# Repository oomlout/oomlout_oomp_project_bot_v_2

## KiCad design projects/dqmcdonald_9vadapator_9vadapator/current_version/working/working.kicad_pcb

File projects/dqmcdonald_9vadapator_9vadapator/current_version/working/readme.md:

# 9vadapator
 
## summary 
* id: dqmcdonald_9vadapator_9vadapator
* user: dqmcdonald
* name: 9vadapator
* board: 9vadapator
* repo: https://github.com/dqmcdonald/9VAdapator
* src_file_repo_kicad_pcb: 9VAdapator.kicad_pcb
* src_file_repo_kicad_pcb_link: https://github.com/dqmcdonald/9VAdapator/tree/master/9VAdapator.kicad_pcb

* src_file_repo_sch: 9VAdapator.sch
* src_file_repo_sch_link: https://github.com/dqmcdonald/9VAdapator/tree/master/9VAdapator.sch
* full details link: https://github.com/oomlout/oomlout_oomp_project_bot_v_2/tree/main/projects/dqmcdonald_9vadapator_9vadapator/current_version/working

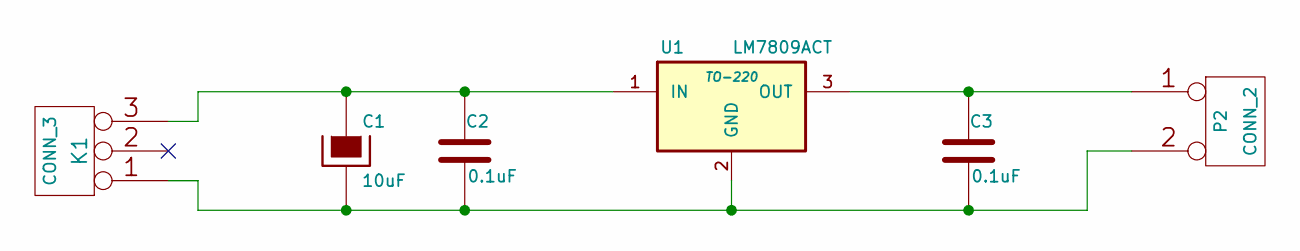
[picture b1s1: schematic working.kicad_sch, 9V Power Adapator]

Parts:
C1: 10uF
C2, C3: 0.1uF
K1: CONN_3
P2: CONN_2
U1: LM7809ACT; TO-220

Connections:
unnamed: C1.1, C2.1, K1.3, U1.1 (IN)
unnamed: C1.2, C2.2, C3.2, K1.1, P2.2 (GND), U1.2 (GND)
unnamed: C3.1, P2.1 (VCC), U1.3 (OUT)

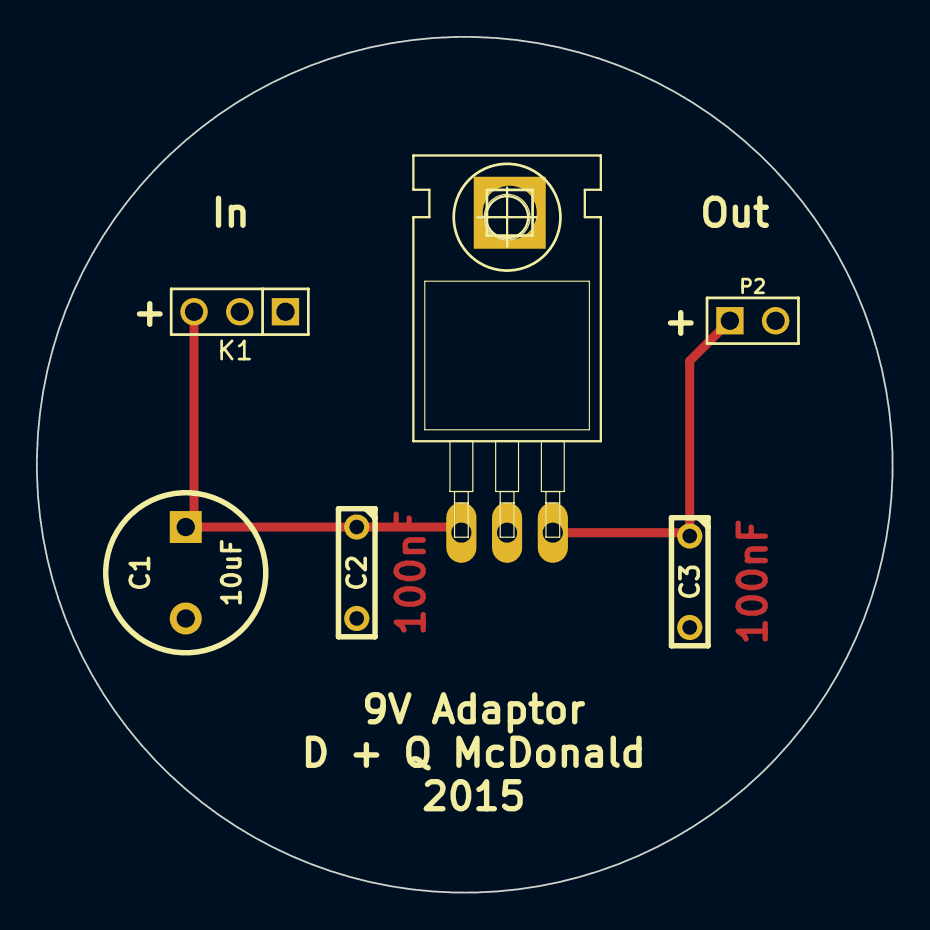
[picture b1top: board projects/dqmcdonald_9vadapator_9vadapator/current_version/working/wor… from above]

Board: 2 copper layers, 47.5 x 47.5 mm, 6 parts (0 on the bottom side), 3 nets.

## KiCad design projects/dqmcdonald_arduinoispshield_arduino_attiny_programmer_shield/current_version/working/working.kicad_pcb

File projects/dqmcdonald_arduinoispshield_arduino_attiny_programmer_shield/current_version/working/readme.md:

# arduinoispshield
 
## summary 
* id: dqmcdonald_arduinoispshield_arduino_attiny_programmer_shield
* user: dqmcdonald
* name: arduinoispshield
* board: arduino_attiny_programmer_shield
* repo: https://github.com/dqmcdonald/ArduinoISPShield
* src_file_repo_kicad_pcb: Arduino ATTINY Programmer Shield.kicad_pcb
* src_file_repo_kicad_pcb_link: https://github.com/dqmcdonald/ArduinoISPShield/tree/master/Arduino ATTINY Programmer Shield.kicad_pcb

* src_file_repo_sch: Arduino ATTINY Programmer Shield.sch
* src_file_repo_sch_link: https://github.com/dqmcdonald/ArduinoISPShield/tree/master/Arduino ATTINY Programmer Shield.sch
* full details link: https://github.com/oomlout/oomlout_oomp_project_bot_v_2/tree/main/projects/dqmcdonald_arduinoispshield_arduino_attiny_programmer_shield/current_version/working

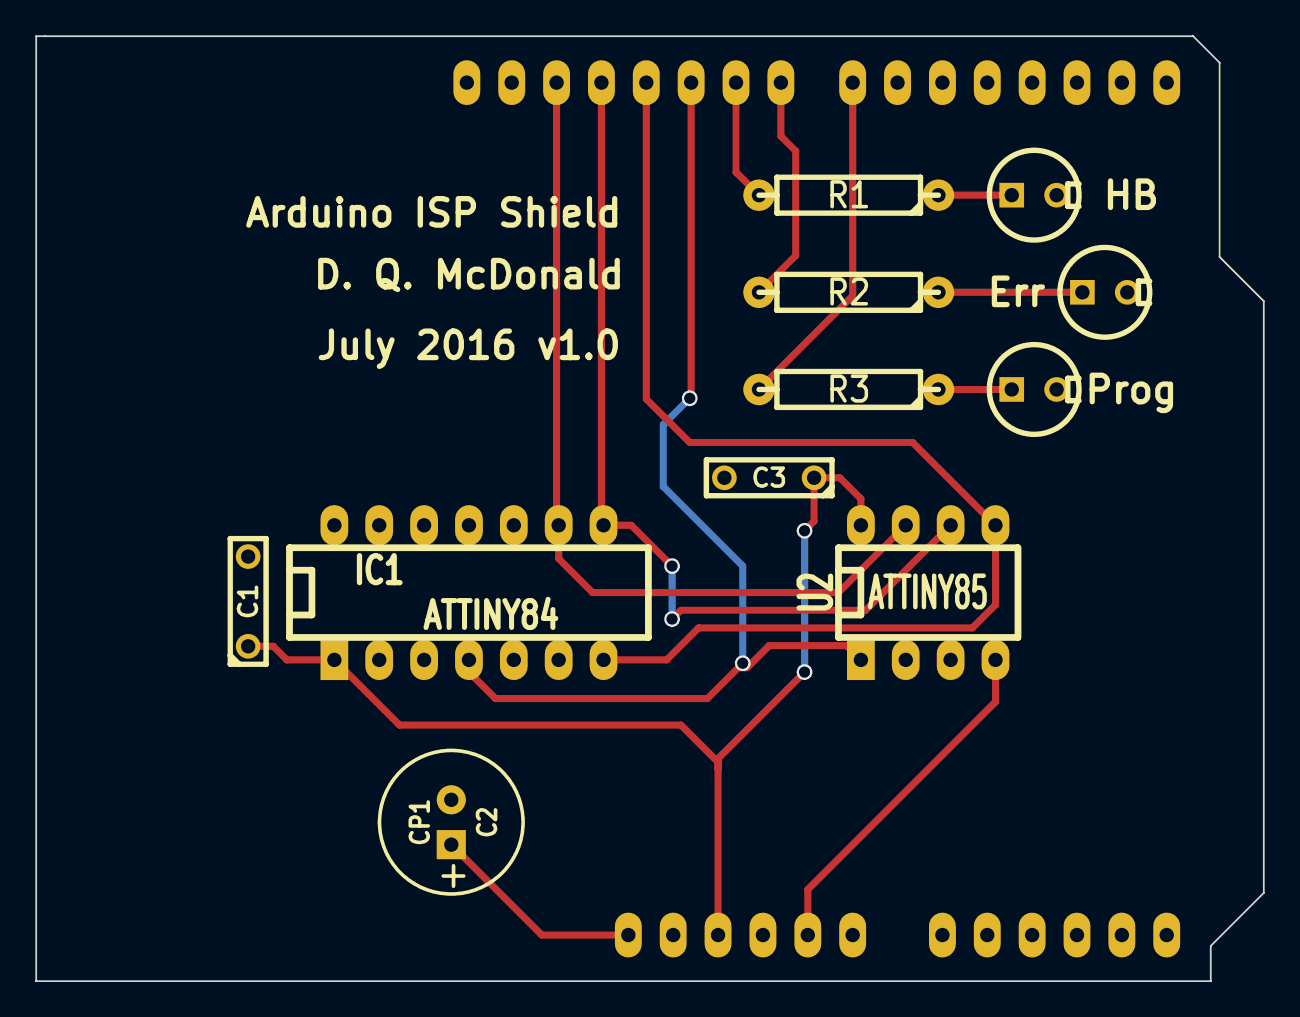
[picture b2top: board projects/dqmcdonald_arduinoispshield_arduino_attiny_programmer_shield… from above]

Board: 2 copper layers, 69.5 x 53.5 mm, 12 parts (0 on the bottom side), 13 nets.

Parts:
C1: 100nf; C2
C2: CP1; C1V8
C3: 100nF; C2
D3: LED; LEDV
Error: LED; LEDV
HeartBeat: LED; LEDV
IC1: ATTINY84; DIP-14__300_ELL
R1: 200R; R4-LARGE_PADS
R2, R3: 220R; R4-LARGE_PADS
SHIELD1: ARDUINO_SHIELD; ARDUINO_SHIELD_2
U2: ATTINY85; DIP-8__300_ELL

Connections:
5V: C1.1, C3.1, IC1.1, SHIELD1.5V, U2.8
GND: C1.2, C2.2, C3.2, D3.2, Error.2, HeartBeat.2, IC1.14, SHIELD1.GND2, U2.4
unnamed: HeartBeat.1, R1.1
unnamed: Error.1, R2.1
unnamed: D3.1, R3.1
Pin7: R3.2, SHIELD1.7
Pin8: R2.2, SHIELD1.8
Pin9: R1.2, SHIELD1.9
Pin10: IC1.4, SHIELD1.10, U2.1
Pin11: IC1.7, SHIELD1.11, U2.5
Pin12: IC1.8, SHIELD1.12, U2.6
Pin13: IC1.9, SHIELD1.13, U2.7
Reset: C2.1, SHIELD1.RST

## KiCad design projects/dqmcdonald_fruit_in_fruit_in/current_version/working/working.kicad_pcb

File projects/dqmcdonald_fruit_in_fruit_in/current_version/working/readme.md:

# fruit_in
 
## summary 
* id: dqmcdonald_fruit_in_fruit_in
* user: dqmcdonald
* name: fruit_in
* board: fruit_in
* repo: https://github.com/dqmcdonald/Fruit-In
* src_file_repo_kicad_pcb: Fruit-In.kicad_pcb
* src_file_repo_kicad_pcb_link: https://github.com/dqmcdonald/Fruit-In/tree/master/Fruit-In.kicad_pcb

* src_file_repo_sch: Fruit-In.sch
* src_file_repo_sch_link: https://github.com/dqmcdonald/Fruit-In/tree/master/Fruit-In.sch
* full details link: https://github.com/oomlout/oomlout_oomp_project_bot_v_2/tree/main/projects/dqmcdonald_fruit_in_fruit_in/current_version/working

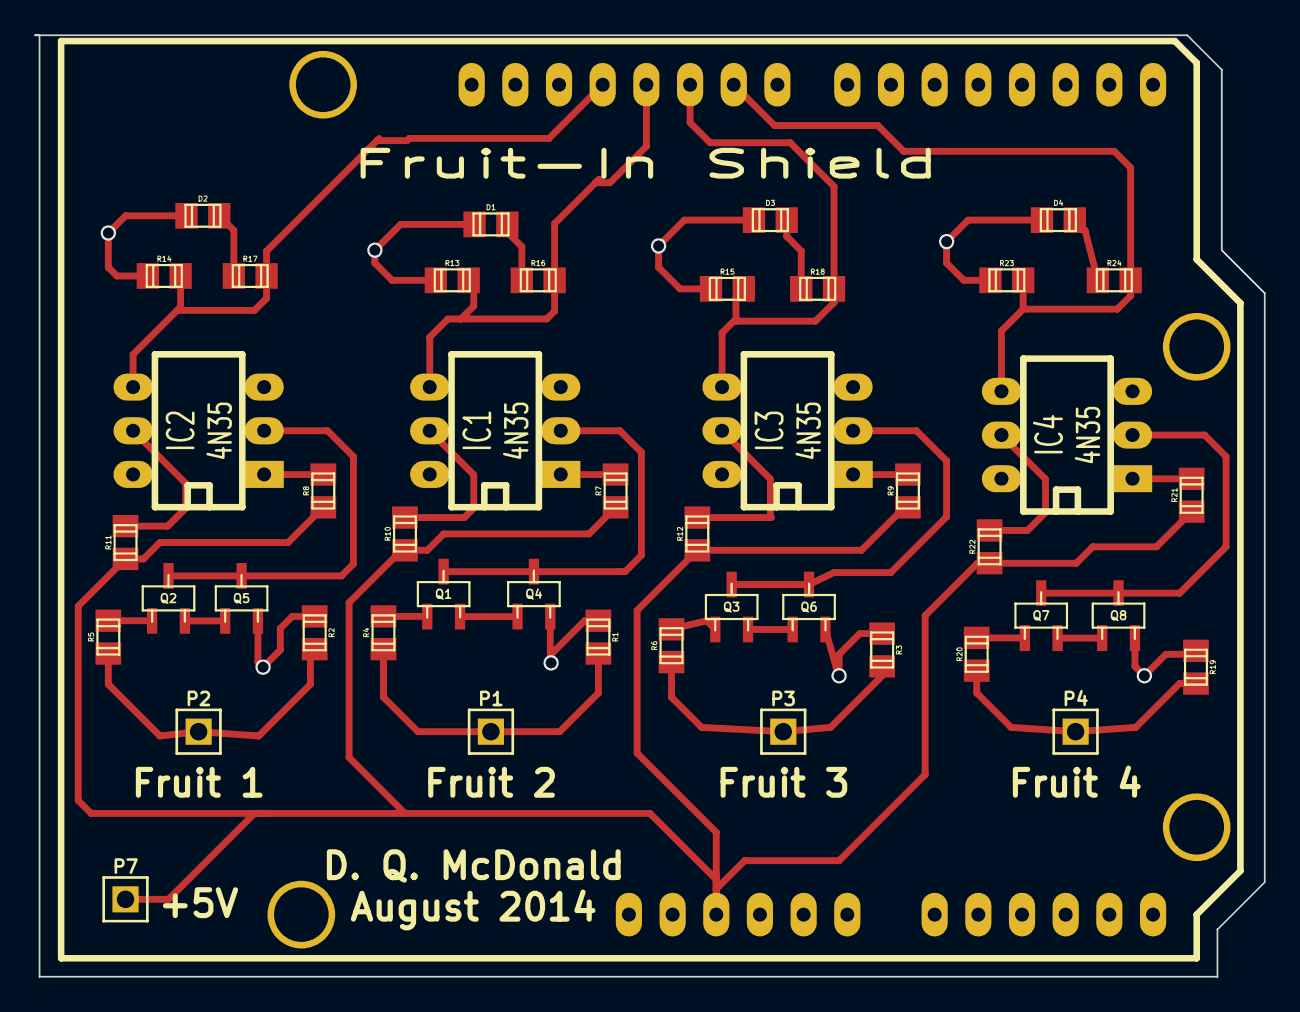
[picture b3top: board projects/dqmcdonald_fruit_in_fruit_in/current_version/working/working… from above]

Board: 2 copper layers, 71.5 x 54.8 mm, 45 parts (0 on the bottom side), 34 nets.

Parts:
D1, D2, D3, D4: LED; c_0805
IC1, IC2, IC3, IC4: 4N35; DIP-6__300_ELL
P1, P2, P3, P4, P7: CONN_1; PIN_ARRAY_1
Q1, Q2, Q3, Q4, Q5, Q6, Q7, Q8: 2N3904; sot23
R1, R2, R3, R19: 2.2M; c_0805
R4, R5, R6, R13, R14, R15, R20, R23: 10K; c_0805
R7, R8, R9, R10, R11, R12, R21, R22: 220 Ohms; c_0805
R16, R17, R18, R24: 470 Ohms; c_0805

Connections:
+5V: P7.1, R7.2, R8.2, R9.2, R10.2, R11.2, R12.2, R21.2, R22.2
D9: IC4.4, R23.1, R24.1
D10: IC3.4, R15.1, R18.1
D11: IC1.4, R13.1, R16.1
D12: IC2.4, R14.1, R17.1
GND: D1.2, D2.2, D3.2, D4.2, Q4.1, Q5.1, Q6.1, Q8.1, R1.2, R2.2, R3.2, R13.2, R14.2, R15.2, R19.2, R23.2
unnamed: D1.1, R16.2
unnamed: D2.1, R17.2
unnamed: D3.1, R18.2
unnamed: D4.1, R24.2
unnamed: IC1.1, R7.1
unnamed: IC1.2, Q1.3, Q4.3
unnamed: IC1.5, R10.1
unnamed: IC2.1, R8.1
unnamed: IC2.2, Q2.3, Q5.3
unnamed: IC2.5, R11.1
unnamed: IC3.1, R9.1
unnamed: IC3.2, Q3.3, Q6.3
unnamed: IC3.5, R12.1
unnamed: IC4.1, R21.1
unnamed: IC4.2, Q7.3, Q8.3
unnamed: IC4.5, R22.1
unnamed: P1.1, R1.1, R4.2
unnamed: P2.1, R2.1, R5.2
unnamed: P3.1, R3.1, R6.2
unnamed: P4.1, R19.1, R20.2
unnamed: Q1.1, Q4.2
unnamed: Q1.2, R4.1
unnamed: Q2.1, Q5.2
unnamed: Q2.2, R5.1
unnamed: Q3.1, Q6.2
unnamed: Q3.2, R6.1
unnamed: Q7.1, Q8.2
unnamed: Q7.2, R20.1

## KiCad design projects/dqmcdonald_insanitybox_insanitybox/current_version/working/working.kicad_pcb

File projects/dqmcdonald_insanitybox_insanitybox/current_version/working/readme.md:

# insanitybox
 
## summary 
* id: dqmcdonald_insanitybox_insanitybox
* user: dqmcdonald
* name: insanitybox
* board: insanitybox
* repo: https://github.com/dqmcdonald/InsanityBox
* src_file_repo_kicad_pcb: InsanityBox.kicad_pcb
* src_file_repo_kicad_pcb_link: https://github.com/dqmcdonald/InsanityBox/tree/master/InsanityBox.kicad_pcb

* src_file_repo_sch: InsanityBox.sch
* src_file_repo_sch_link: https://github.com/dqmcdonald/InsanityBox/tree/master/InsanityBox.sch
* full details link: https://github.com/oomlout/oomlout_oomp_project_bot_v_2/tree/main/projects/dqmcdonald_insanitybox_insanitybox/current_version/working

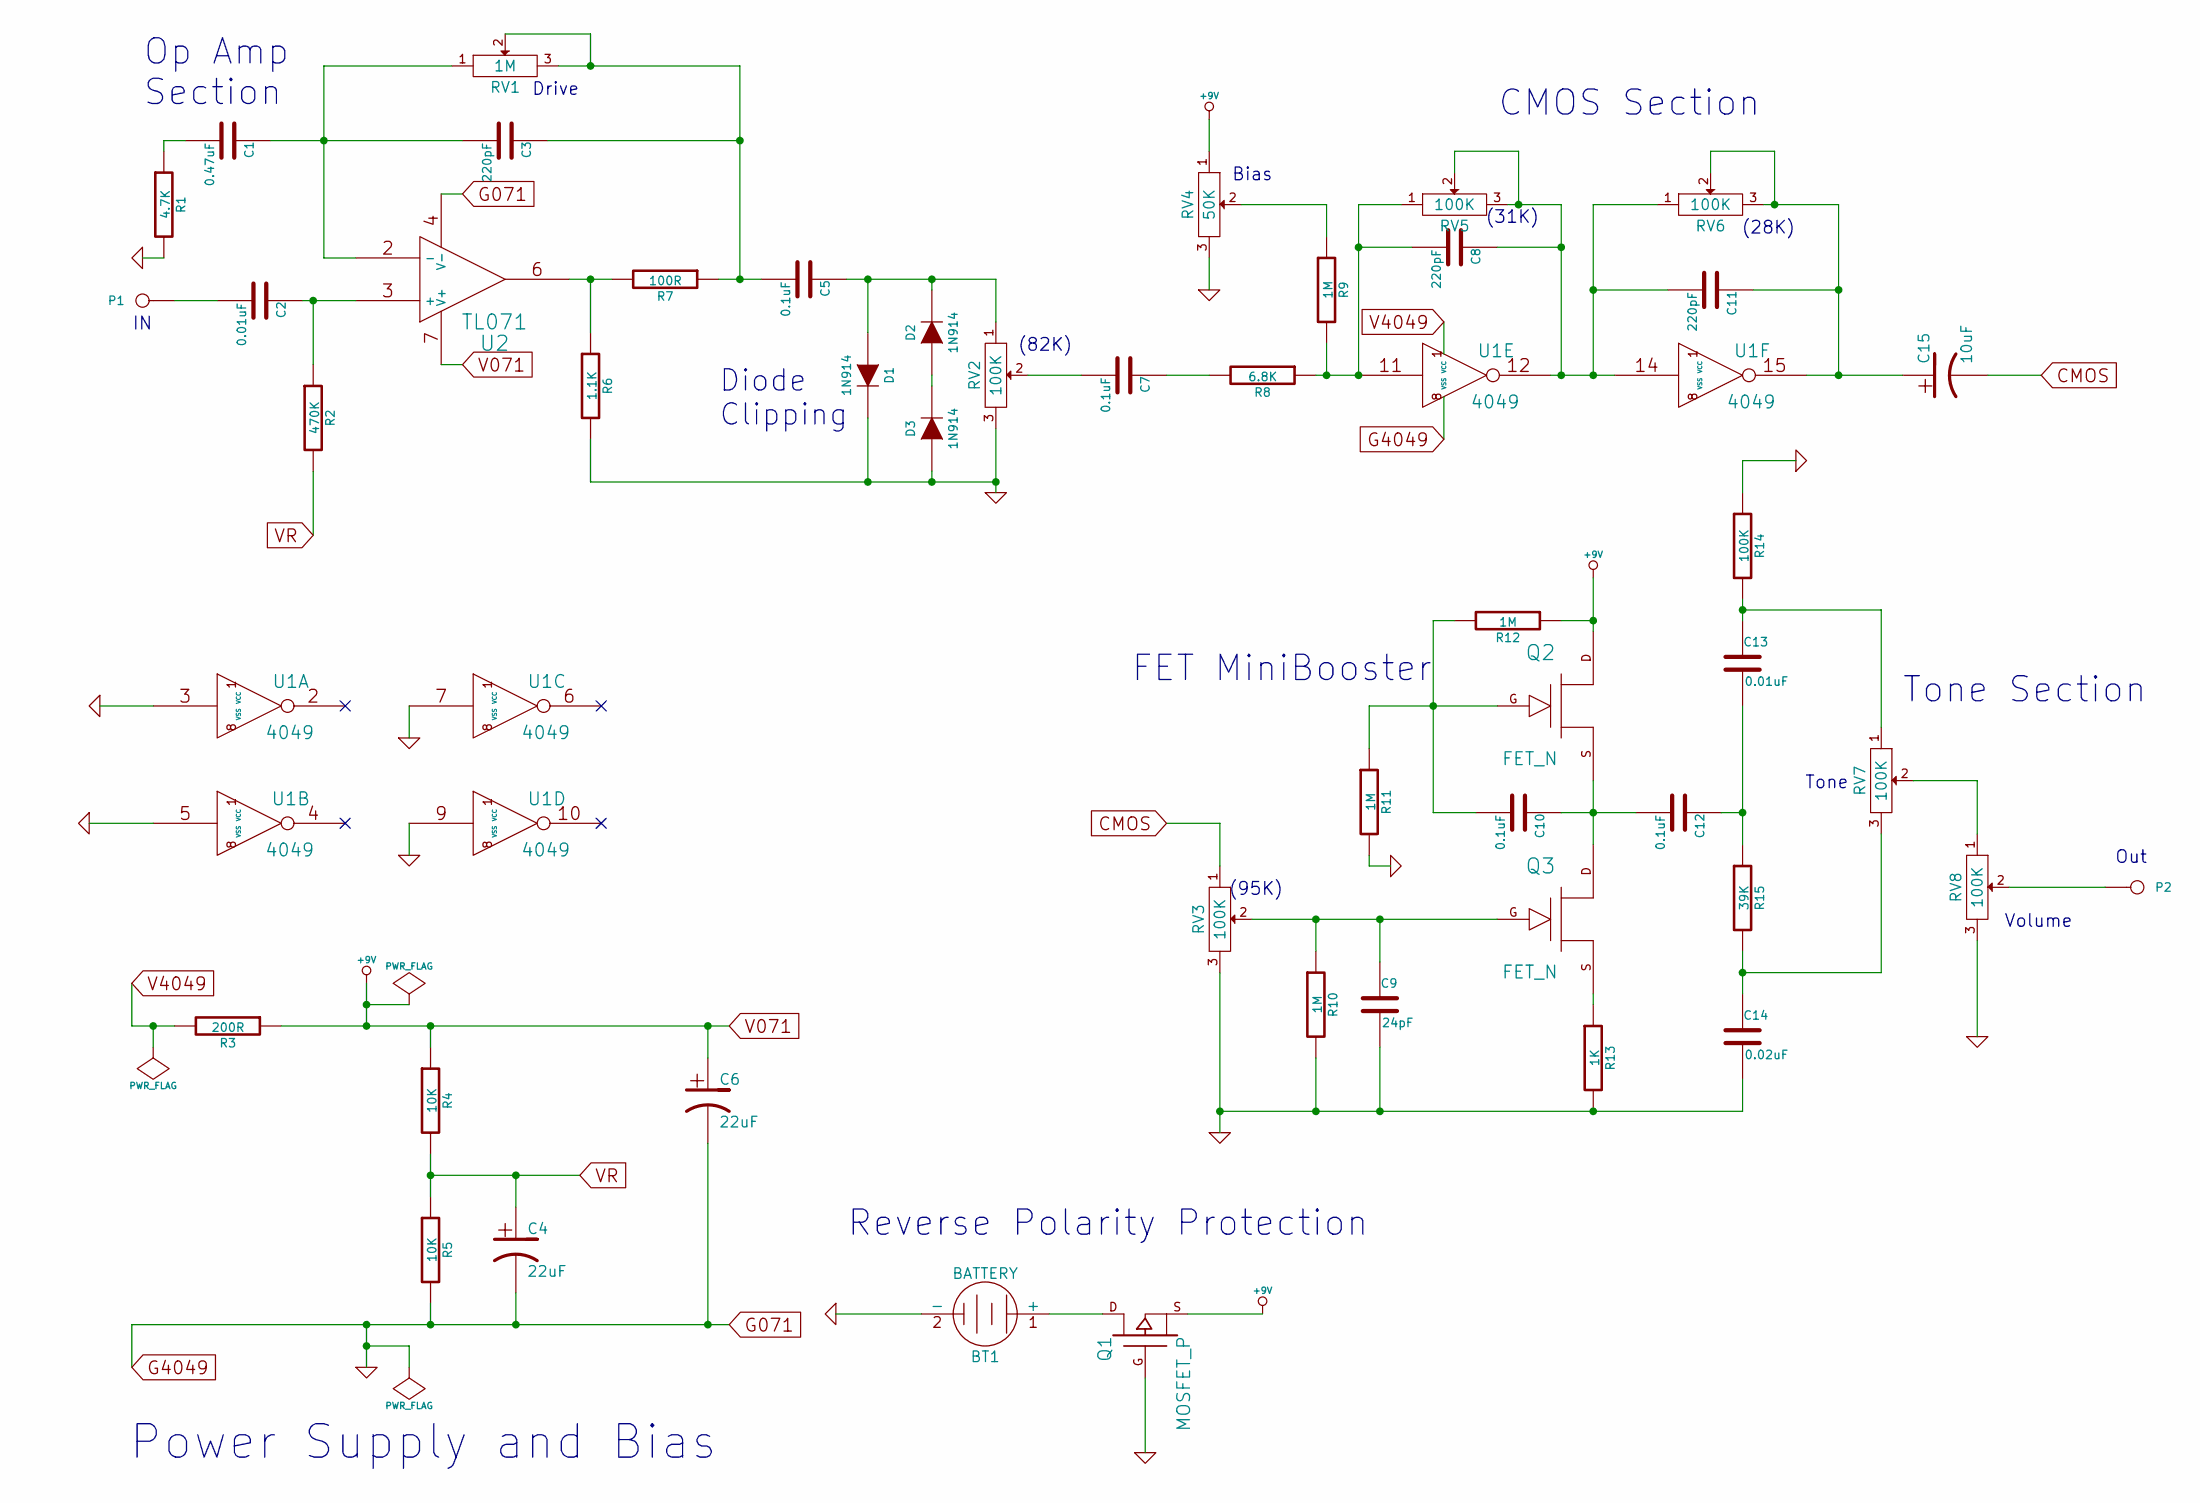
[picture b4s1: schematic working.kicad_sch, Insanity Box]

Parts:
BT1: BATTERY; Pin_Header_Straight_1x02
C1: 0.47uF; C_0805
C2, C13: 0.01uF; C_0805
C3, C8, C11: 220pF; C_0805
C4, C6: 22uF; c_elec_5x5.3
C5, C7, C10, C12: 0.1uF; C_0805
C9: 24pF; C_0805
C14: 0.02uF; C_0805
C15: 10uF; c_elec_6.3x5.7
D1, D2, D3: 1N914; SOD-323
P1, P2: CONN_1; Pin_Header_Straight_1x01
Q1: MOSFET_P; pChannelMostfetSot23
Q2, Q3: FET_N; SOT-23_J201_JFET
R1: 4.7K; R_0805_HandSoldering
R2: 470K; R_0805_HandSoldering
R3: 200R; R_0805_HandSoldering
R4, R5: 10K; R_0805_HandSoldering
R6: 1.1K; R_0805_HandSoldering
R7: 100R; R_0805_HandSoldering
R8: 6.8K; R_0805_HandSoldering
R9, R10, R11, R12: 1M; R_0805_HandSoldering
R13: 1K; R_0805_HandSoldering
R14: 100K; R_0805_HandSoldering
R15: 39K; R_0805_HandSoldering
RV1: 1M; Pin_Header_Straight_1x03
RV2, RV3, RV5, RV6, RV7, RV8: 100K; Pin_Header_Straight_1x03
RV4: 50K; Pin_Header_Straight_1x03
U1: 4049; SO-16-N
U2: TL071; SOIC-8-N

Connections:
CMOS: C15.2, RV3.1
G071: BT1.2 (-), C4.2, C6.2, C9.2, C14.2, D1.2 (K), D3.1 (A), Q1.G, R1.2, R5.2, R6.2, R10.2, R11.2, R13.2, R14.1, RV2.3, RV3.3, RV4.3, RV8.3, U1.3, U1.5, U1.7, U1.8 (VSS), U1.9, U2.4 (V-)
unnamed: BT1.1 (+), Q1.D
unnamed: C1.1, C3.2, RV1.1, U2.2 (-)
unnamed: C1.2, R1.1
unnamed: C2.1, R2.1, U2.3 (+)
unnamed: C2.2, P1.1
unnamed: C3.1, C5.2, R7.1, RV1.2, RV1.3
unnamed: C5.1, D1.1 (A), D2.2 (K), RV2.1
unnamed: C7.1, R8.2
unnamed: C7.2, RV2.2
unnamed: C8.2, R8.1, R9.2, RV5.1, U1.11
unnamed: C9.1, Q3.G, R10.1, RV3.2
unnamed: C10.1, C12.2, Q2.S, Q3.D
unnamed: C10.2, Q2.G, R11.1, R12.2
unnamed: C11.1, C15.1, RV6.2, RV6.3, U1.15
unnamed: C8.1, C11.2, RV5.2, RV5.3, RV6.1, U1.12, U1.14
unnamed: C12.1, C13.2, R15.1
unnamed: C13.1, R14.2, RV7.1
unnamed: C14.1, R15.2, RV7.3
unnamed: D2.1 (A), D3.2 (K)
unnamed: P2.1, RV8.2
unnamed: Q3.S, R13.1
unnamed: R6.1, R7.2, U2.6
unnamed: R9.1, RV4.2
unnamed: RV7.2, RV8.1
V071: C6.1, Q1.S, Q2.D, R3.1, R4.1, R12.1, RV4.1, U2.7 (V+)
V4049: R3.2, U1.1 (VCC)
VR: C4.1, R2.2, R4.2, R5.1

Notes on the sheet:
Tone Section
Diode Clipping
(31K)
FET MiniBooster
Volume
Bias
Tone
(28K)
Power Supply and Bias
(95K)
(82K)
Reverse Polarity Protection
Drive
Op Amp Section
Out
CMOS Section

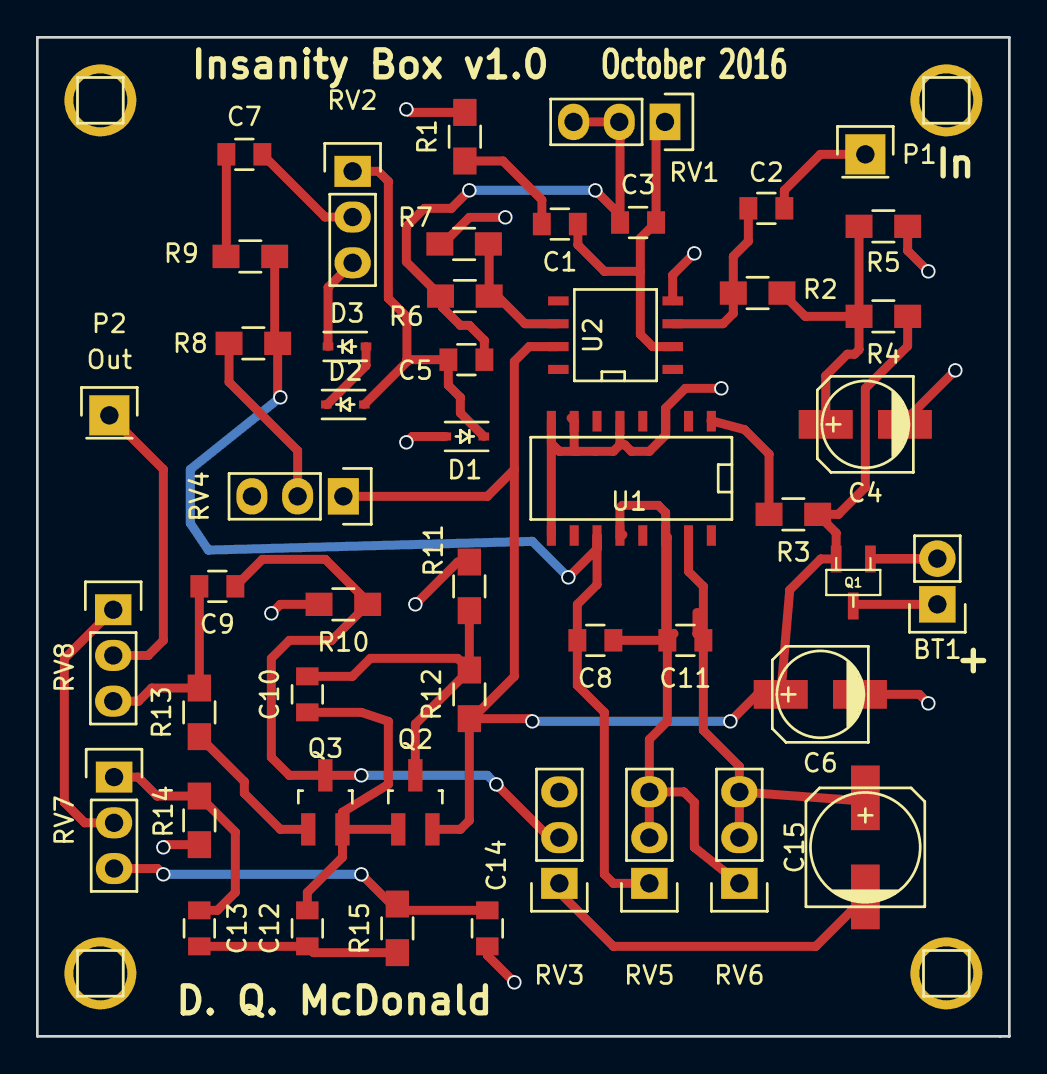
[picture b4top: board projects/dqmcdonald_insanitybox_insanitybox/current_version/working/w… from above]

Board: 2 copper layers, 54.0 x 55.5 mm, 49 parts (0 on the bottom side), 29 nets.

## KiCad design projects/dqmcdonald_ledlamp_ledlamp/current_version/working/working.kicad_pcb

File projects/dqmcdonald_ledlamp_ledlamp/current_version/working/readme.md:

# ledlamp
 
## summary 
* id: dqmcdonald_ledlamp_ledlamp
* user: dqmcdonald
* name: ledlamp
* board: ledlamp
* repo: https://github.com/dqmcdonald/LEDLamp
* src_file_repo_kicad_pcb: LEDLamp.kicad_pcb
* src_file_repo_kicad_pcb_link: https://github.com/dqmcdonald/LEDLamp/tree/master/LEDLamp.kicad_pcb

* src_file_repo_sch: LEDLamp.sch
* src_file_repo_sch_link: https://github.com/dqmcdonald/LEDLamp/tree/master/LEDLamp.sch
* full details link: https://github.com/oomlout/oomlout_oomp_project_bot_v_2/tree/main/projects/dqmcdonald_ledlamp_ledlamp/current_version/working

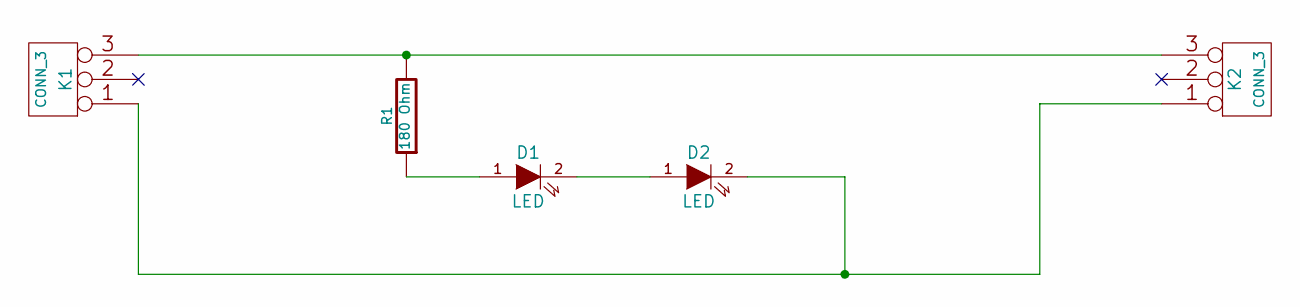
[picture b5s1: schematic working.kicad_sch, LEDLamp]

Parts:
D1, D2: LED
K1, K2: CONN_3
R1: 180 Ohm

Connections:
unnamed: D1.1 (A), R1.1
unnamed: D1.2 (K), D2.1 (A)
unnamed: D2.2 (K), K1.1, K2.1
unnamed: K1.3, K2.3, R1.2

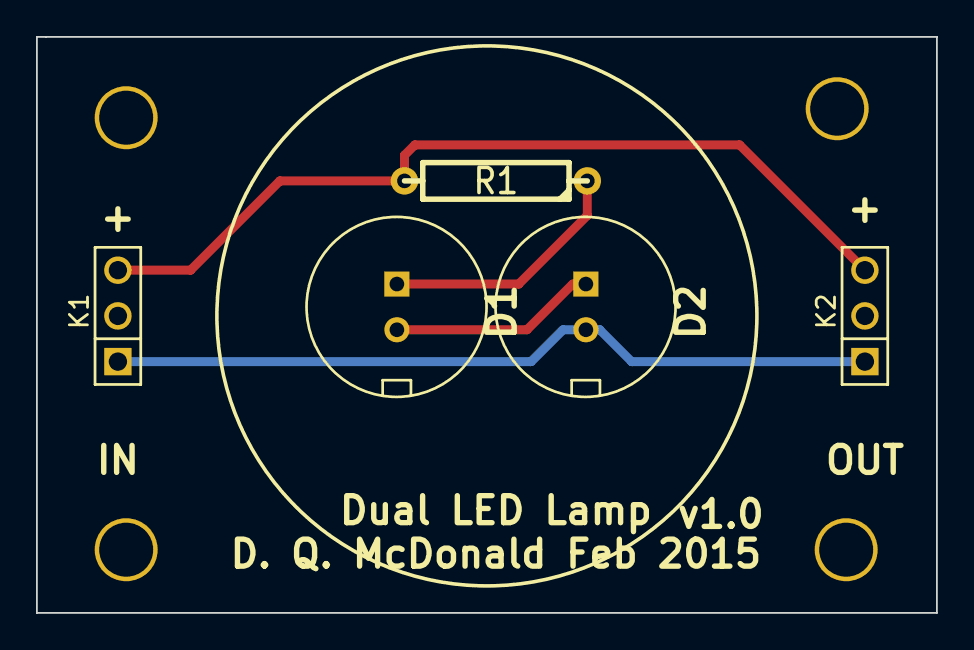
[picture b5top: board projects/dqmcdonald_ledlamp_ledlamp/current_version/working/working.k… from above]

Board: 2 copper layers, 50.0 x 32.0 mm, 5 parts (0 on the bottom side), 4 nets.

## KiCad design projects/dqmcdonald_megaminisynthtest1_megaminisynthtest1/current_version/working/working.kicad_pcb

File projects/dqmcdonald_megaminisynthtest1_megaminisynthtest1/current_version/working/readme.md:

# megaminisynthtest1
 
## summary 
* id: dqmcdonald_megaminisynthtest1_megaminisynthtest1
* user: dqmcdonald
* name: megaminisynthtest1
* board: megaminisynthtest1
* repo: https://github.com/dqmcdonald/MegaMiniSynthTest1
* src_file_repo_kicad_pcb: MegaMiniSynthTest1.kicad_pcb
* src_file_repo_kicad_pcb_link: https://github.com/dqmcdonald/MegaMiniSynthTest1/tree/master/MegaMiniSynthTest1.kicad_pcb

* src_file_repo_sch: MegaMiniSynthTest1.sch
* src_file_repo_sch_link: https://github.com/dqmcdonald/MegaMiniSynthTest1/tree/master/MegaMiniSynthTest1.sch
* full details link: https://github.com/oomlout/oomlout_oomp_project_bot_v_2/tree/main/projects/dqmcdonald_megaminisynthtest1_megaminisynthtest1/current_version/working

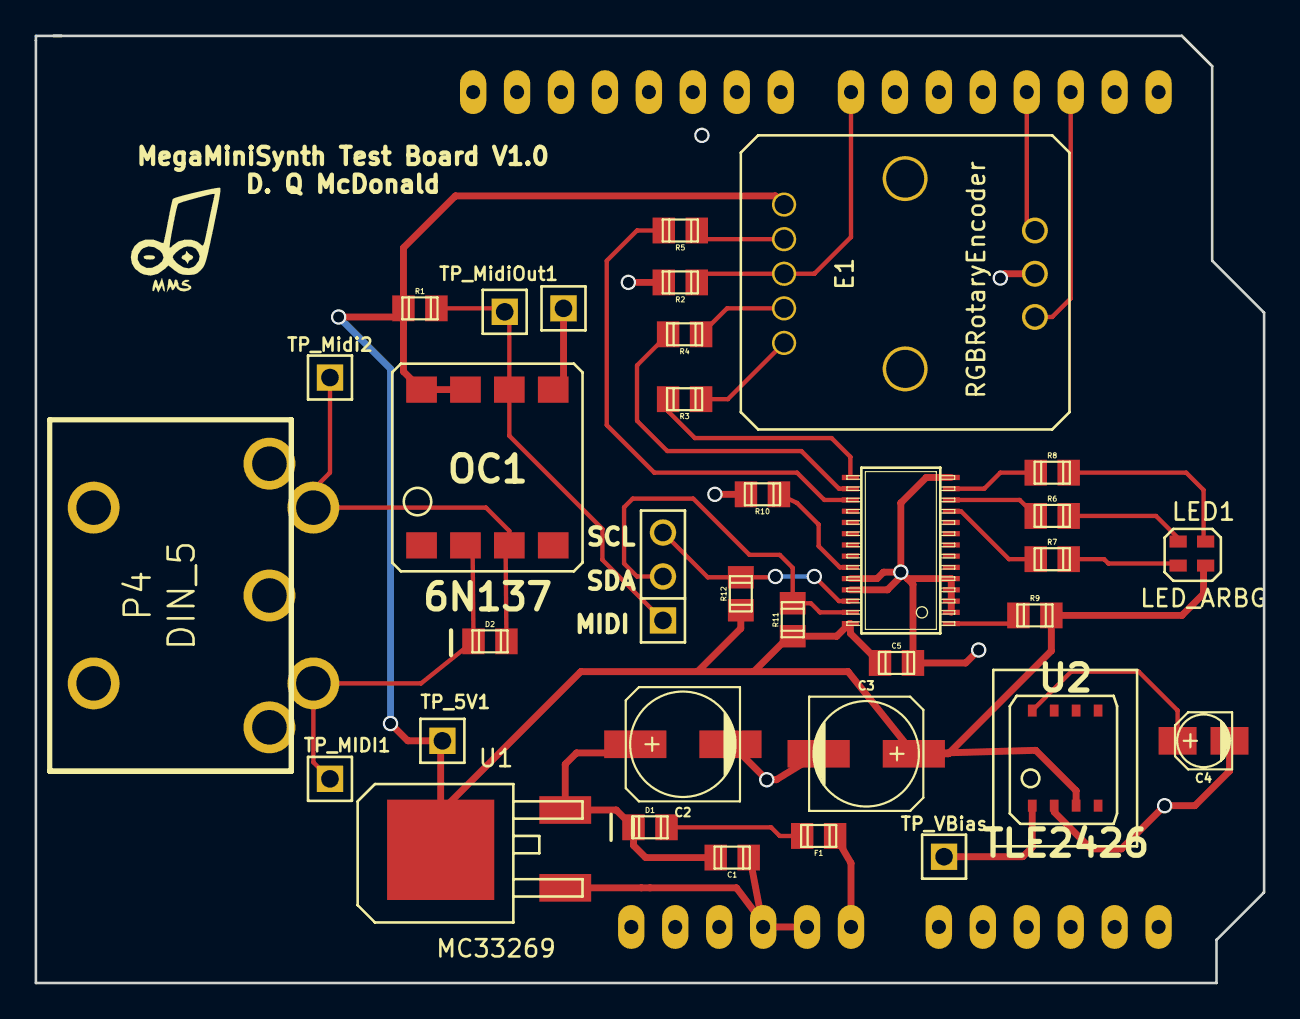
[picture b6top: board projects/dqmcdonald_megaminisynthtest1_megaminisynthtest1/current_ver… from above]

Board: 2 copper layers, 71.0 x 54.8 mm, 32 parts (0 on the bottom side), 26 nets.

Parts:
C1: 100n; c_0805
C2, C3: 47uF; c_elec_6.3x5.8
C4: 1uF; c_elec_3x5.3
C5: 100nf; c_0805
D1, D2: DIODE; c_0805
E1: RGBRotaryEncoder
F1: FERRITE; c_0805
LED1: LED_ARBG; SMDRGBLED
OC1: 6N137
P4: DIN_5
R1: 8k2; c_0805
R2, R10: 10K; c_0805
R3, R7, R8: 200; c_0805
R4, R5: 100; c_0805
R6: 300; c_0805
R9: 10k; c_0805
R11, R12: 4k7; c_0805
TP_5V1: PIN_ARRAY_1
TP_MIDI1: PIN_ARRAY_1
TP_Midi2: PIN_ARRAY_1
TP_MidiOut1: PIN_ARRAY_1
TP_VBias: PIN_ARRAY_1
U1: MC33269
U2: TLE2426
U3: PCA9685; -TSSOP28

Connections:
+5V: C3.1, C5.2, E1.5, LED1.1, OC1.7, OC1.8, R1.2, R9.1, R11.2, R12.2, TP_5V1.1, U1.2, U2.3, U3.28
Arduino7: E1.3, R2.2
GND: C1.2, C2.2, C3.2, C4.2, C5.1, E1.7, OC1.5, R2.1, R10.1, U1.1, U2.2, U3.2, U3.3, U3.4, U3.5, U3.14, U3.24, U3.25
unnamed: C4.1, U2.8
unnamed: D1.1, F1.1
unnamed: D2.1, OC1.3, P4.5, TP_Midi2.1
unnamed: D2.2, OC1.2, P4.4, TP_MIDI1.1
unnamed: E1.1, R3.2
unnamed: E1.2, R4.2
unnamed: E1.4, R5.2
unnamed: LED1.2, R6.1
unnamed: LED1.3, R8.1
unnamed: LED1.4, R7.1
unnamed: R3.1, U3.15
unnamed: R4.1, U3.16
unnamed: R5.1, U3.17
unnamed: R6.2, U3.12
unnamed: R7.2, U3.11
unnamed: R8.2, U3.13
unnamed: R9.2, U3.1
unnamed: R10.2, U3.23
SCL: R12.1, U3.26
SDA: R11.1, U3.27
Serial2: OC1.6, R1.1, TP_MidiOut1.1
VBias: TP_VBias.1, U2.1
VCC: C1.1, C2.1, D1.2, U1.3

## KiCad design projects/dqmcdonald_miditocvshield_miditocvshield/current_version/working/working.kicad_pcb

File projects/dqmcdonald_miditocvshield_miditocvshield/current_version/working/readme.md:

# miditocvshield
 
## summary 
* id: dqmcdonald_miditocvshield_miditocvshield
* user: dqmcdonald
* name: miditocvshield
* board: miditocvshield
* repo: https://github.com/dqmcdonald/MidiToCVShield
* src_file_repo_kicad_pcb: MidiToCVShield.kicad_pcb
* src_file_repo_kicad_pcb_link: https://github.com/dqmcdonald/MidiToCVShield/tree/master/MidiToCVShield.kicad_pcb

* src_file_repo_sch: MidiToCVShield.sch
* src_file_repo_sch_link: https://github.com/dqmcdonald/MidiToCVShield/tree/master/MidiToCVShield.sch
* full details link: https://github.com/oomlout/oomlout_oomp_project_bot_v_2/tree/main/projects/dqmcdonald_miditocvshield_miditocvshield/current_version/working

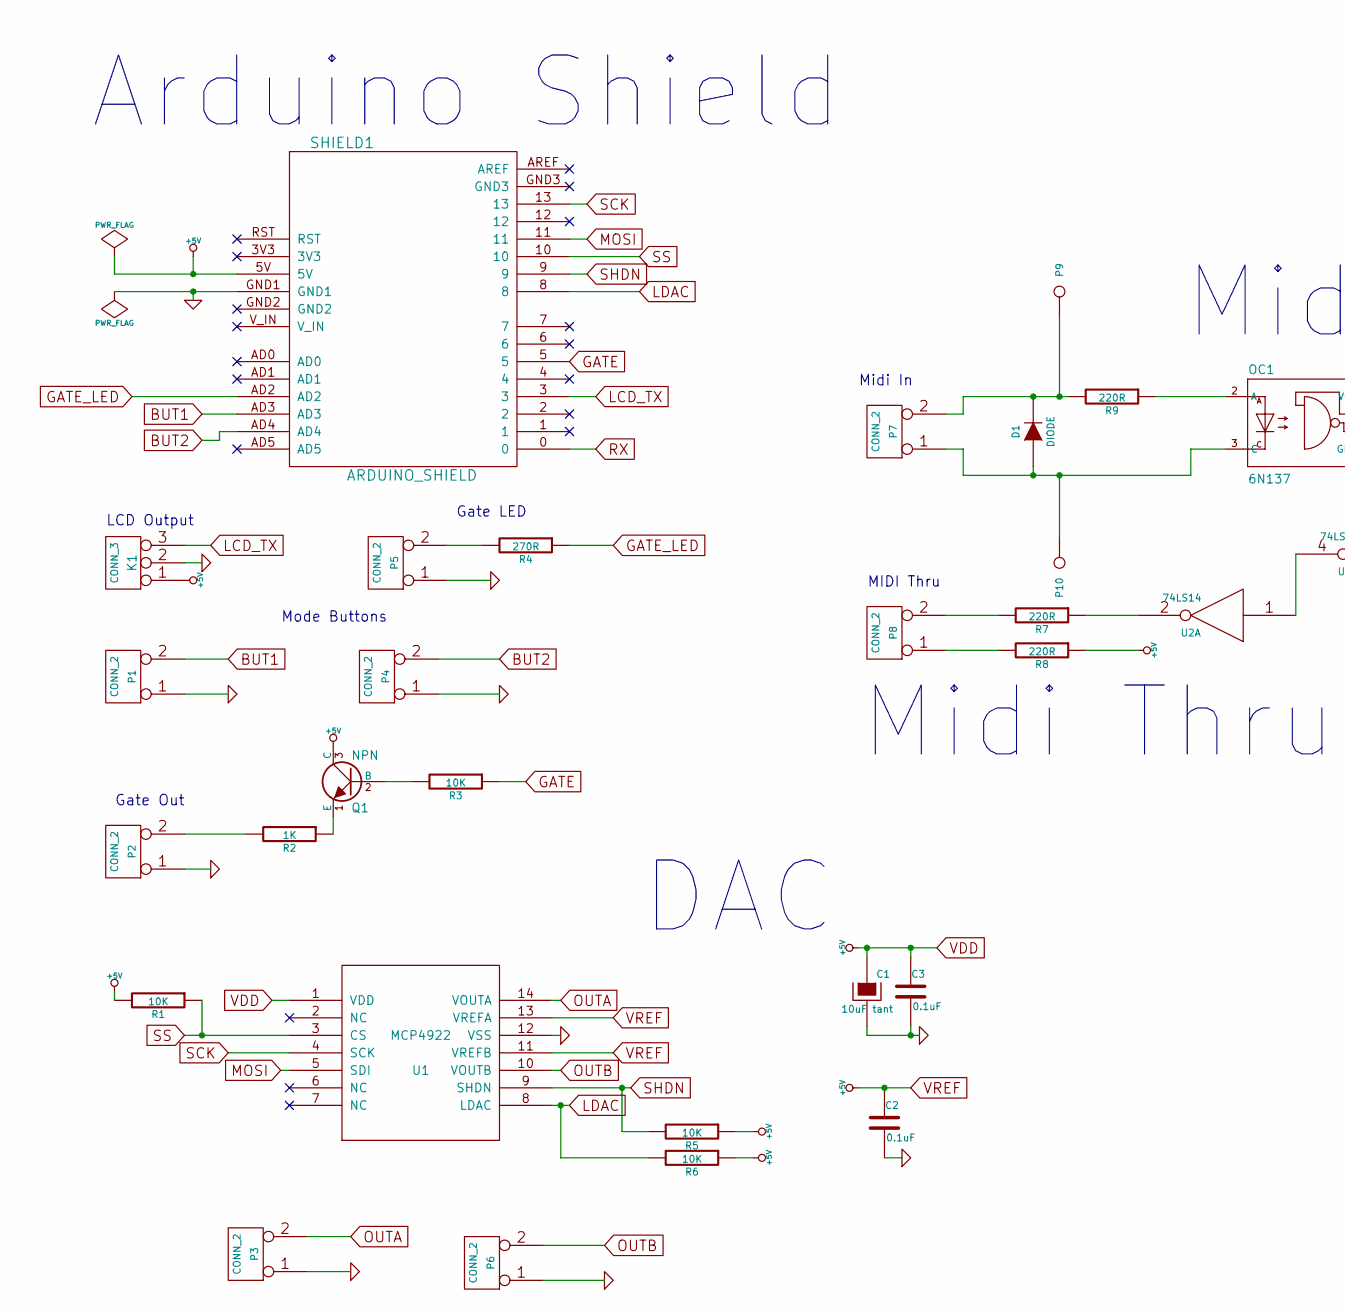
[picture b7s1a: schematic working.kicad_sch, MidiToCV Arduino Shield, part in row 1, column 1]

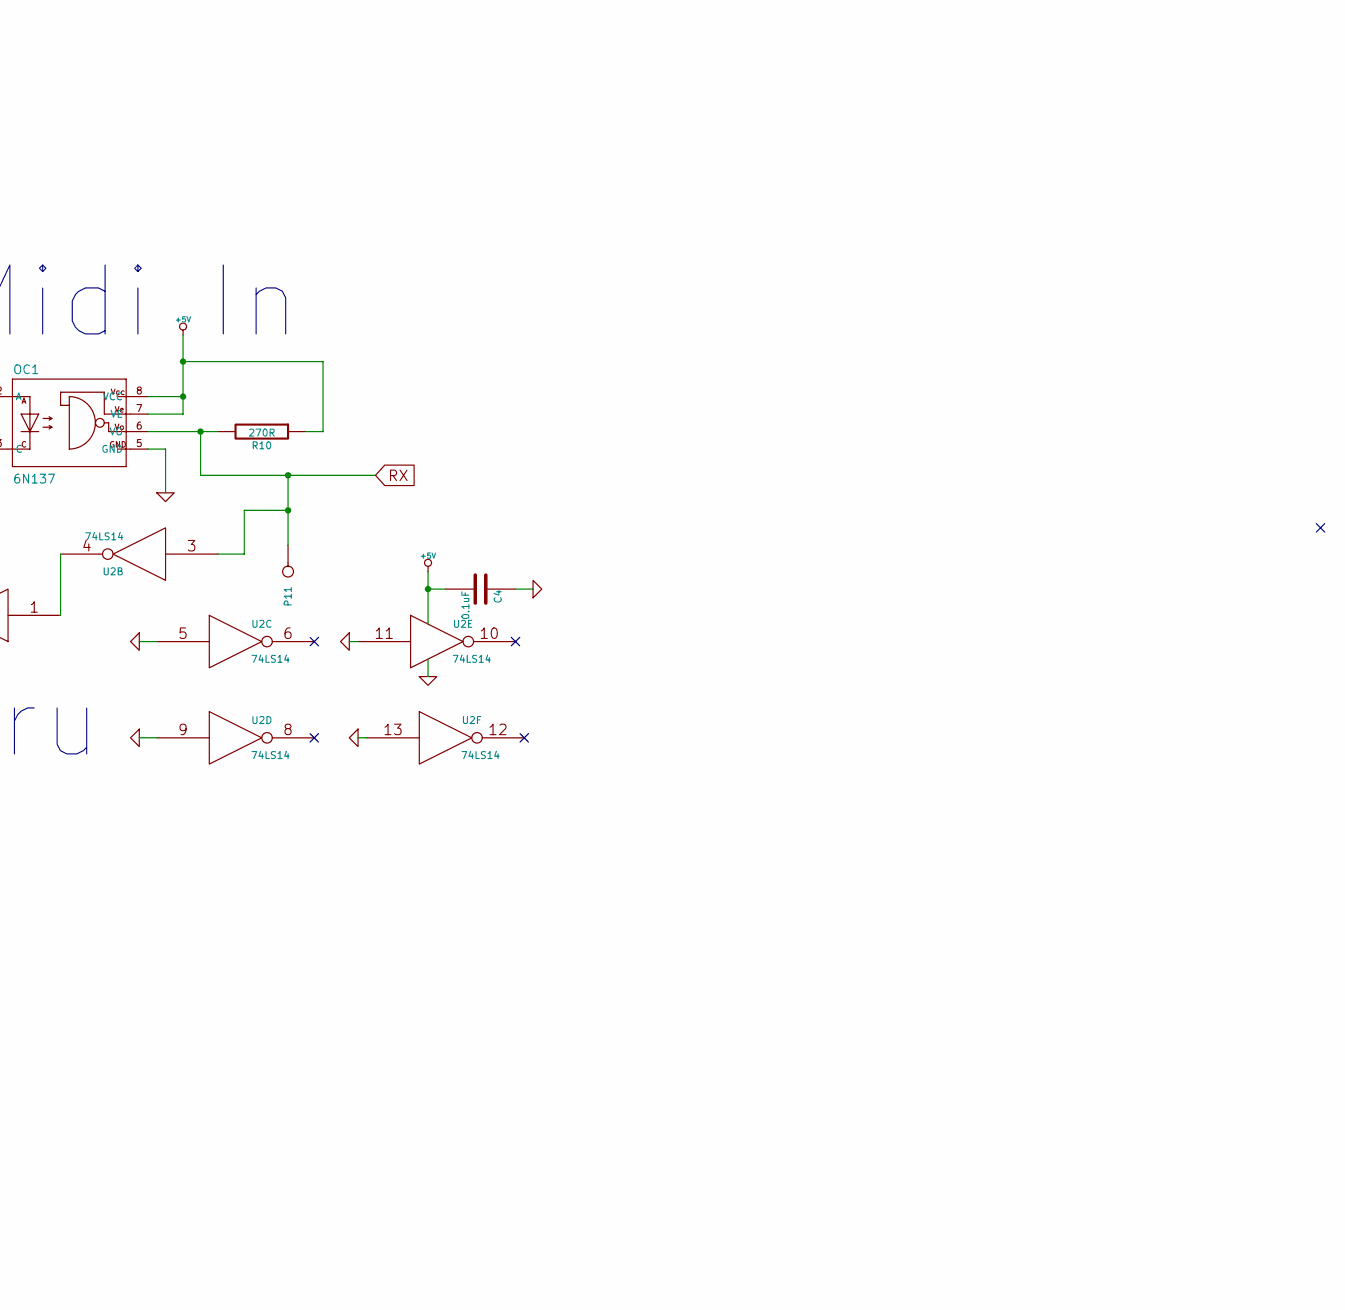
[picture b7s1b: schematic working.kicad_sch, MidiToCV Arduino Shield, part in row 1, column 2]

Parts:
C1: 10uF tant
C2, C3, C4: 0.1uF
D1: DIODE
K1: CONN_3
OC1: 6N137; optocoupler-DIL08
P1, P2, P3, P4, P5, P6, P7, P8: CONN_2
P9, P10, P11: CONN_1
Q1: NPN
R1, R3, R5, R6: 10K
R2: 1K
R4, R10: 270R
R7, R8, R9: 220R
SHIELD1: ARDUINO_SHIELD
U1: MCP4922; MODULE
U2: 74LS14

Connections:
BUT1: P1.2 (GND), SHIELD1.AD3
BUT2: P4.2 (GND), SHIELD1.AD4
GATE: R3.1, SHIELD1.5
GATE_LED: R4.1, SHIELD1.AD2
GND: C1.2, C2.2, C3.2, C4.1, K1.2 (PM), OC1.5 (GND), P1.1 (VCC), P2.1 (VCC), P3.1 (VCC), P4.1 (VCC), P5.1 (VCC), P6.1 (VCC), SHIELD1.GND1, U1.12 (VSS), U2.5, U2.7 (GND), U2.9, U2.11, U2.13
LCD_TX: K1.3, SHIELD1.3
LDAC: R6.2, SHIELD1.8, U1.8 (LDAC)
MOSI: SHIELD1.11, U1.5 (SDI)
unnamed: D1.1 (A), OC1.3 (C), P7.1 (VCC), P10.1
unnamed: D1.2 (K), P7.2 (GND), P9.1, R9.2
unnamed: OC1.2 (A), R9.1
unnamed: P2.2 (GND), R2.2
unnamed: P5.2 (GND), R4.2
unnamed: P8.1 (VCC), R8.2
unnamed: P8.2 (GND), R7.2
unnamed: Q1.1 (E), R2.1
unnamed: Q1.2 (B), R3.2
unnamed: R7.1, U2.2
unnamed: U2.1, U2.4
OUTA: P3.2 (GND), U1.14 (VOUTA)
OUTB: P6.2 (GND), U1.10 (VOUTB)
RX: OC1.6 (VO), P11.1, R10.2, SHIELD1.0, U2.3
SCK: SHIELD1.13, U1.4 (SCK)
SHDN: R5.2, SHIELD1.9, U1.9 (SHDN)
SS: R1.1, SHIELD1.10, U1.3 (CS)
VDD: C1.1, C2.1, C3.1, C4.2, K1.1, OC1.7 (VE), OC1.8 (VCC), Q1.3 (C), R1.2, R5.1, R6.1, R8.1, R10.1, SHIELD1.5V, U1.1 (VDD), U1.11 (VREFB), U1.13 (VREFA), U2.14 (VCC)

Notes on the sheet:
Gate LED
MIDI Thru
Gate Out
Arduino Shield
Midi In
Midi Thru
Mode Buttons
DAC
LCD Output

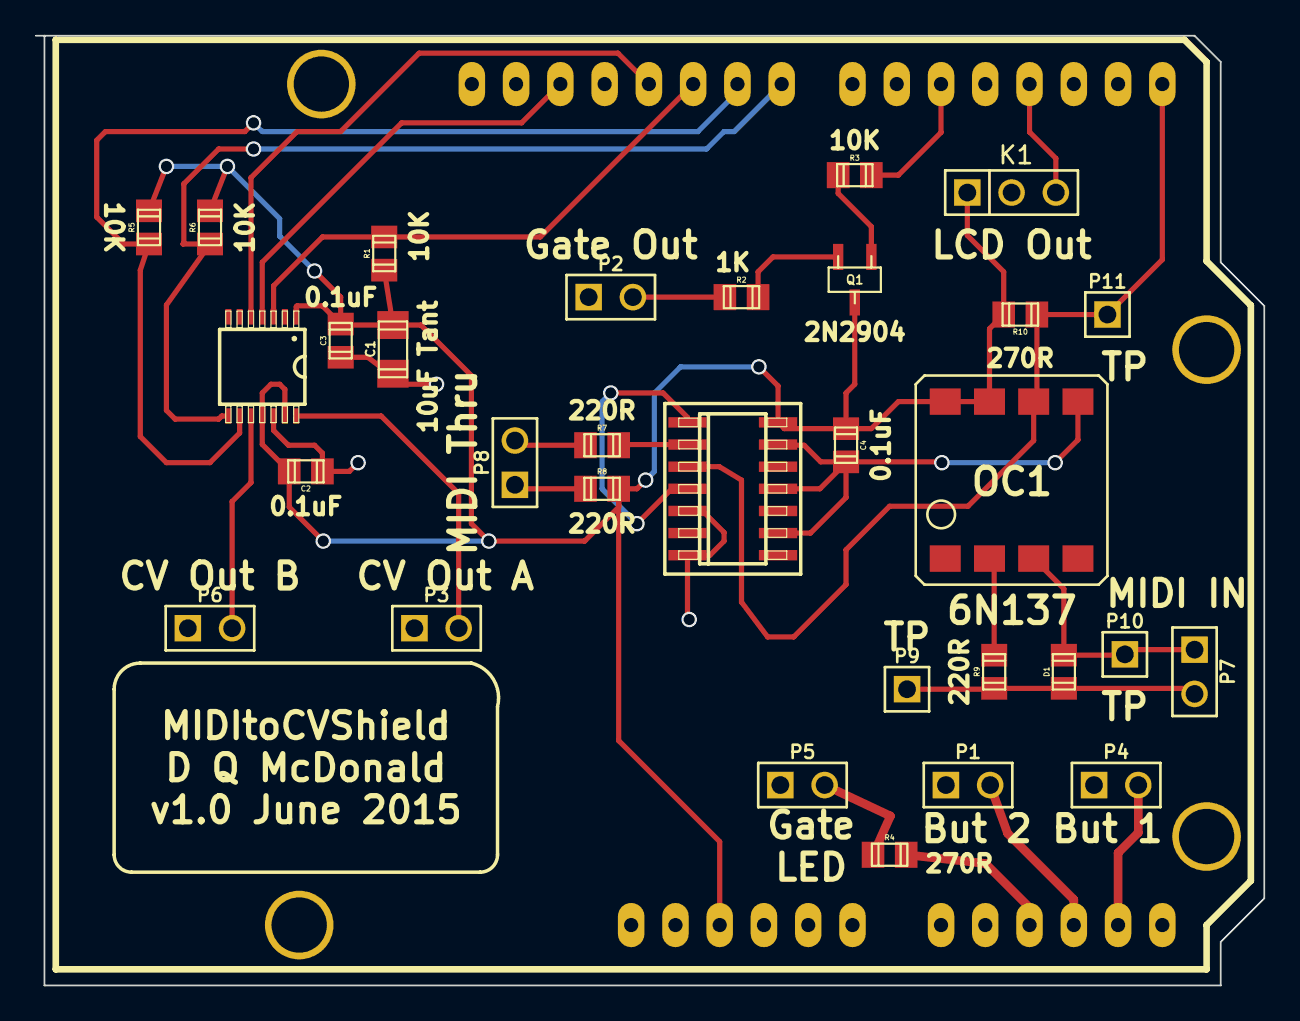
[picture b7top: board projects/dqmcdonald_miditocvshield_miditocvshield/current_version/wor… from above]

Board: 2 copper layers, 70.0 x 54.5 mm, 31 parts (0 on the bottom side), 19 nets.
